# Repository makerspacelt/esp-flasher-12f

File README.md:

This is ESP-12F interface to connect with the [esp-flasher](http://esp-flasher.makerspace.lt/repo), featuring pogo-pin snap-on design.

* Designed to snap on top of any ESP-12F module without any provisions for programming or debugging in-place

Support this open-source project - buy your fully assembled and tested device [here](http://esp-12f.makerspace.lt/shop)

Dev NOTE: before commit, run `./kibot.sh` to regenerate documentation, gerbers and other assets.

* [schematics.pdf](gen/schematics.pdf)
* [pcb.pdf with dimensions](gen/pcb.pdf)

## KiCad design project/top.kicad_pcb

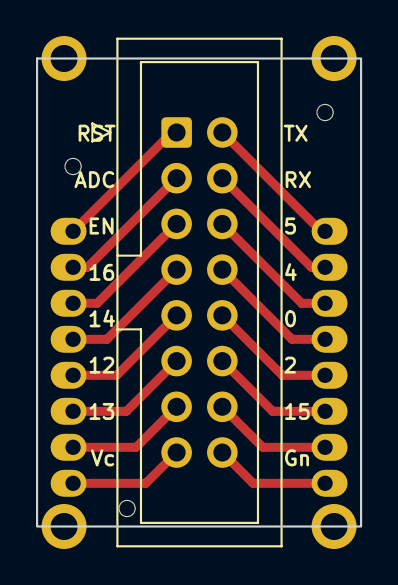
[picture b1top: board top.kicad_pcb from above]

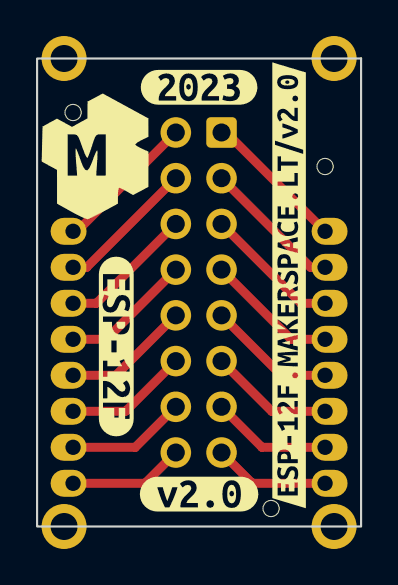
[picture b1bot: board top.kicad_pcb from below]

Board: 2 copper layers, 18.0 x 26.0 mm, 8 parts (5 on the bottom side), 16 nets.

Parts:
G2: LOGO_KMS; logo_kms_small_silkscreen
J1: IDC 2x8; IDC-Header_2x08_P2.54mm_Vertical
SYM1: board_outline; board
U1: top; esp-top
kibuzzard-642C0B87: G***; kibuzzard-642C0B87
kibuzzard-642C03EC: G***; kibuzzard-642C03EC
kibuzzard-642C03F5: G***; kibuzzard-642C03F5
kibuzzard-642C04F0: G***; kibuzzard-642C04F0

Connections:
ADC: J1.3, U1.2 (ADC)
EN: J1.5, U1.3 (EN)
GND: J1.16, U1.9 (GND)
IO0: J1.10, U1.12 (GPIO0)
IO2: J1.12, U1.11 (GPIO2)
IO4: J1.8, U1.13 (GPIO4)
IO5: J1.6, U1.14 (GPIO5)
IO12: J1.11, U1.6 (GPIO12)
IO13: J1.13, U1.7 (GPIO13)
IO14: J1.9, U1.5 (GPIO14)
IO15: J1.14, U1.10 (GPIO15)
IO16: J1.7, U1.4 (GPIO16)
RST: J1.1, U1.1 (~RST)
RX: J1.4, U1.15 (GPIO3/RXD)
TX: J1.2, U1.16 (GPIO1/TXD)
Vcc: J1.15, U1.8 (VCC)

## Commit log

2023-03-20 adding WIP board without infrastructure or docs
2023-03-28 small size adjustments and labels
2023-03-28 reducing top holes to 0.8
2023-04-04 splitting boards into separate projects
2023-04-04 refactoring project and adding automation stuff
2023-04-04 adding generatables
2023-04-04 enlarge top holes(0.85) and pads
2023-04-04 enlarging mag board pads to match the top board
2023-04-06 updating readme with links to related projects
2023-05-12 adding real project photo
2023-05-20 adding CERN-OHL-S v2 license
